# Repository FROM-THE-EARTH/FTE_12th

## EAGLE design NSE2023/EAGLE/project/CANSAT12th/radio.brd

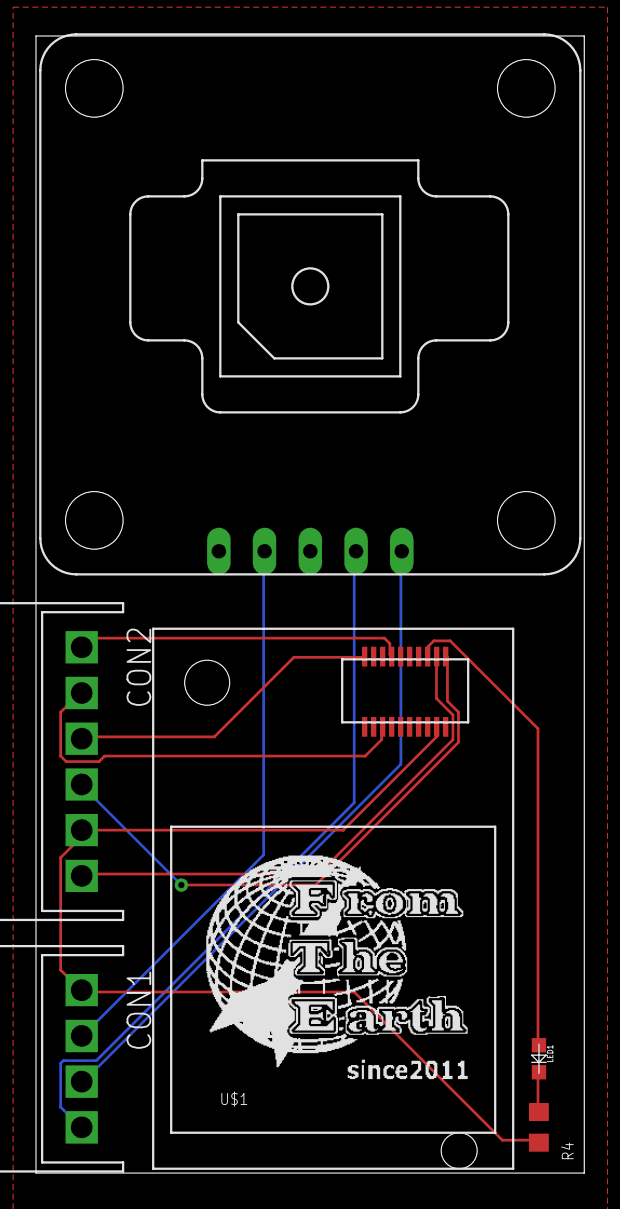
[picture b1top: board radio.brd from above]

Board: 2 copper layers, 30.5 x 63.2 mm, 7 parts (0 on the bottom side), 11 nets.

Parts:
CON1: 4PIN_SIDE
CON2: 6PIN_SIDE
IM: IM920C
LED1: OSXX1608C1A
R4: 100; R0603
U$1: LOGO
U$3: AE-GYSFDMAXB

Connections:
+3V3: CON2.P$6, IM.$P17
+5V: CON1.P$2, U$3.P4
GND: CON1.P$1, CON2.P$5, IM.$P18, R4.1
GPSRX: CON1.P$3, U$3.P2
GPSTX: CON1.P$4, U$3.P1
IM_BUSY: CON2.P$3, IM.$P1
IM_RESET: CON2.P$4, IM.$P19
IM_RX: CON2.P$2, IM.$P6
IM_TX: CON2.P$1, IM.$P7
LED: IM.$P15, LED1.AN
unnamed: LED1.CT, R4.2

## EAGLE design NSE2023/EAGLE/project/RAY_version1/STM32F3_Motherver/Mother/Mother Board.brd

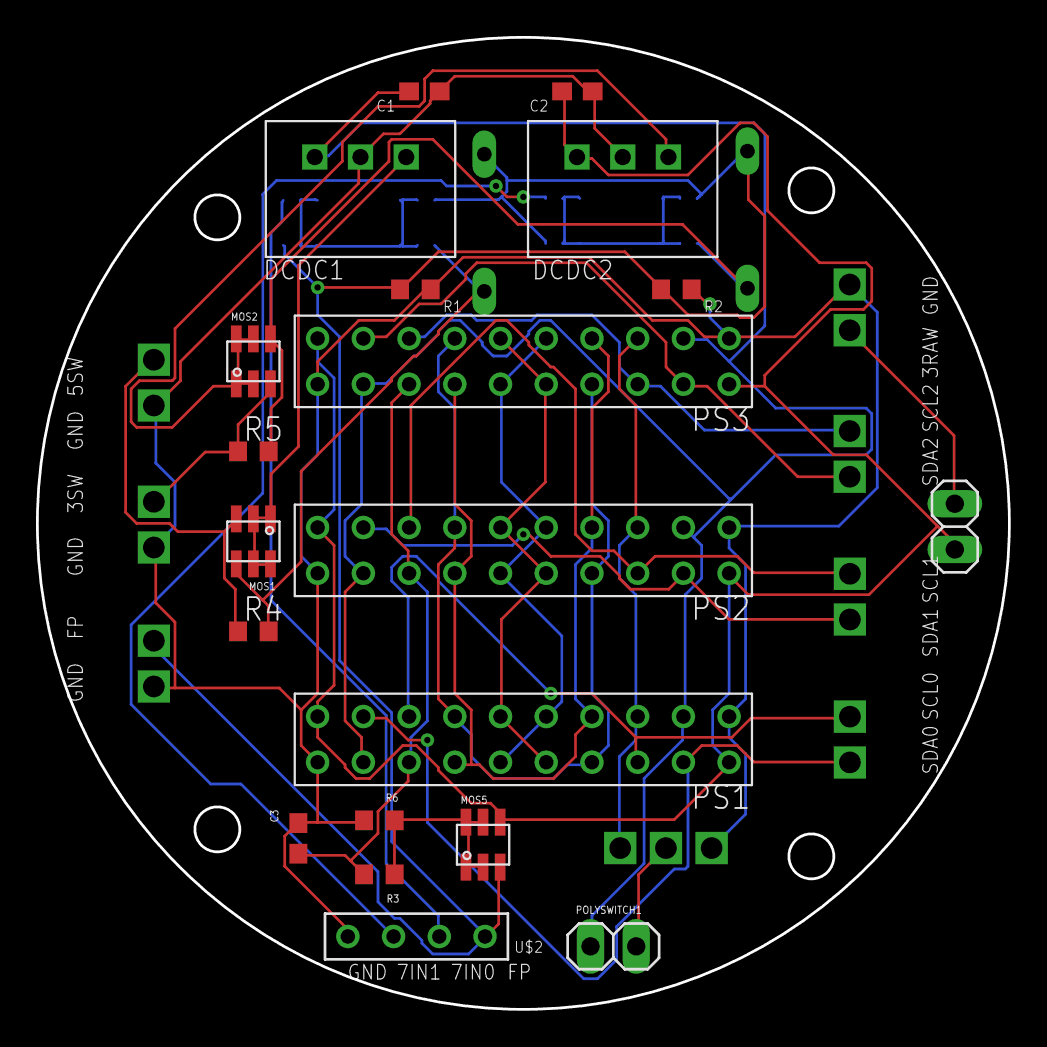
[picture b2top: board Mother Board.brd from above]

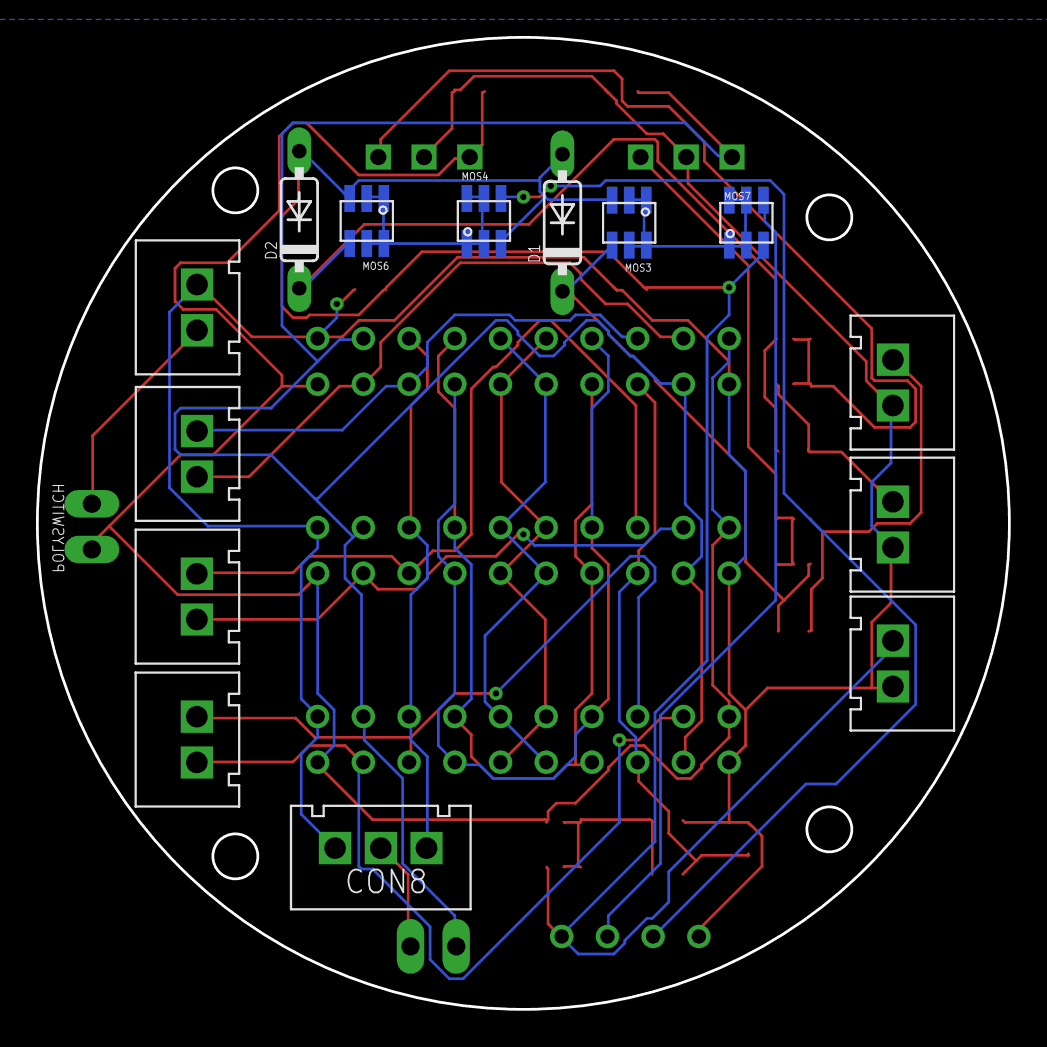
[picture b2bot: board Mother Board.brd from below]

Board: 2 copper layers, 54.0 x 54.0 mm, 34 parts (14 on the bottom side), 29 nets.

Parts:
C1, C2: 3.3uF; C0603
C3: 10uF; C0603
CON1, CON2, CON3, CON4, CON5, CON6, CON7: 2PIN
CON8: 3PIN
D1, D2: 1N4148DO35-7; DO35-7
DCDC1: 5V1A_M78AR05-1
DCDC2: 3.3V1A_M78AR033-1
MOS1, MOS2, MOS3, MOS4, MOS5, MOS6, MOS7: SSM6J808R
POLYSWITCH, POLYSWITCH1: 1X02
PS1, PS2, PS3: 2X10
R1, R2, R3: 1k; R0603
R4, R5: 100k; R0603
R6: 10k; R0603
U$2: 1X4

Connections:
3.3VSW: CON7.P$2, MOS2.3, R5.1
3.3_RAW: CON4.P$2, POLYSWITCH.2
5VSW: CON6.P$2, MOS1.3, R4.1
5V_RAW: CON8.P$2, POLYSWITCH1.2
7.4_0ENT: MOS7.4, U$2.P$2
7.4_1ENT: MOS4.4, U$2.P$3
+3V3: C2.1, DCDC2.VOUT, MOS5.4, POLYSWITCH.1, PS1.P$2, PS1.P$19, PS2.P$2, PS2.P$19, PS3.P$2, PS3.P$19
+5V: C1.1, DCDC1.VOUT, POLYSWITCH1.1, PS1.P$3, PS1.P$18, PS2.P$3, PS2.P$18, PS3.P$3, PS3.P$18
+5V1: DCDC1.VIN, MOS1.1, MOS1.2, MOS1.5, MOS1.6
BIT1: PS1.P$9, PS1.P$12, PS2.P$9, PS2.P$12, PS3.P$9, PS3.P$12
BIT2: PS1.P$7, PS1.P$14, PS2.P$7, PS2.P$14, PS3.P$7, PS3.P$14
FP: CON5.P$2, D1.A, D2.A, MOS3.3, MOS4.3, MOS5.3, MOS6.3, MOS7.3, R1.2, R2.2, U$2.P$1
FP_CHECKER: C3.1, PS1.P$5, PS2.P$5, PS3.P$5, R3.2
GND: C1.2, C2.2, C3.2, CON4.P$1, CON5.P$1, CON6.P$1, CON7.P$1, CON8.P$1, DCDC1.GND, DCDC2.GND, PS1.P$1, PS1.P$20, PS2.P$1, PS2.P$20, PS3.P$1, PS3.P$20, R1.1, R2.1, R6.1, U$2.P$4
LOGRX: PS1.P$8, PS1.P$13, PS2.P$8, PS2.P$13, PS3.P$8, PS3.P$13
LOGTX: PS1.P$10, PS1.P$11, PS2.P$10, PS2.P$11, PS3.P$10, PS3.P$11
unnamed: D2.C, MOS2.4, MOS6.4, R5.2
unnamed: MOS4.1, MOS4.2, MOS4.5, MOS4.6, MOS6.1, MOS6.2, MOS6.5, MOS6.6
unnamed: DCDC2.VIN, MOS2.1, MOS2.2, MOS2.5, MOS2.6
unnamed: D1.C, MOS1.4, MOS3.4, R4.2
unnamed: MOS3.1, MOS3.2, MOS3.5, MOS3.6, MOS7.1, MOS7.2, MOS7.5, MOS7.6
unnamed: MOS5.1, MOS5.2, MOS5.5, MOS5.6, R3.1, R6.2
PWM: CON8.P$3, PS1.P$16, PS2.P$16, PS3.P$16
SCL0: CON1.P$1, PS1.P$6, PS1.P$15
SCL1: CON2.P$1, PS2.P$6, PS2.P$15
SCL2: CON3.P$1, PS3.P$6, PS3.P$15
SDA0: CON1.P$2, PS1.P$4, PS1.P$17
SDA1: CON2.P$2, PS2.P$4, PS2.P$17
SDA2: CON3.P$2, PS3.P$4, PS3.P$17

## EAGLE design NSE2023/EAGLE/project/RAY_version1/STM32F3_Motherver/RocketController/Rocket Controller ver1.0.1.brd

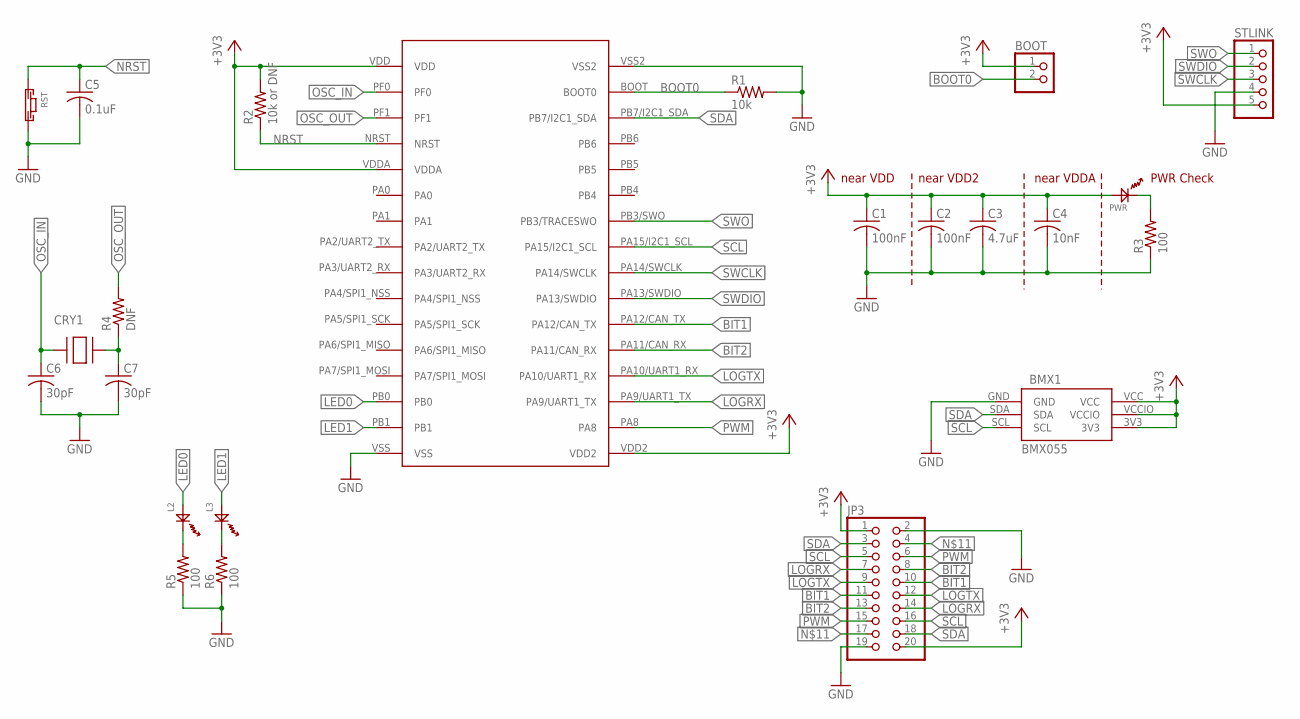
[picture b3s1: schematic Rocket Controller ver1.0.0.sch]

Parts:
BMX1: BMX055
BOOT: PINHD-1X2; 1X02
C1, C2: 100nF; C1608
C3: 4.7uF; C1608
C4: 10nF; C1608
C5: 0.1uF; C1608
C6, C7: 30pF; C1608
CRY1: 8MHZ; CRYSTAL
JP3: PINHD-2X10/90; 2X10/90
L2, L3: OSXX1608C1A
PWR: OSXX1608C1A
R1: 10k; R0603
R2: 10k or DNF; R0603
R3, R5, R6: 100; R0603
R4: DNF; R0603
RST: TVAF06-A020B-R
STLINK: PINHD-1X5; 1X05
U$1: STM32F303K8

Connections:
+3V3: BMX1.3V3, BMX1.VCC, BMX1.VCCIO, BOOT.1, C1.1, C2.1, C3.1, C4.1, JP3.1, JP3.20, PWR.AN, R2.2, STLINK.5, U$1.VDD, U$1.VDD2, U$1.VDDA
BIT1: JP3.10, JP3.11, U$1.PA12/CAN_TX
BIT2: JP3.8, JP3.13, U$1.PA11/CAN_RX
BOOT0: BOOT.2, R1.1, U$1.BOOT (BOOT0)
GND: BMX1.GND, C1.2, C2.2, C3.2, C4.2, C5.2, C6.2, C7.2, JP3.2, JP3.19, R1.2, R3.1, R5.1, R6.1, RST.P$2, STLINK.4, U$1.VSS, U$1.VSS2
LED0: L2.AN, U$1.PB0; also elsewhere on the board
LED1: L3.AN, U$1.PB1; also elsewhere on the board
LOGRX: JP3.7, JP3.14, U$1.PA9/UART1_TX
LOGTX: JP3.9, JP3.12, U$1.PA10/UART1_RX
unnamed: PWR.CT, R3.2
unnamed 10: L2.CT, R5.2; also elsewhere on the board
unnamed: C7.1, CRY1.P$2, R4.1
unnamed 12: L3.CT, R6.2; also elsewhere on the board
unnamed: JP3.4, JP3.17
NRST: C5.1, R2.1, RST.P$1, U$1.NRST
OSC_IN: C6.1, CRY1.P$1, U$1.PF0
OSC_OUT: R4.2, U$1.PF1
SCL: BMX1.SCL, JP3.5, JP3.16, U$1.PA15/I2C1_SCL
SDA: BMX1.SDA, JP3.3, JP3.18, U$1.PB7/I2C1_SDA
SWCLK: STLINK.3, U$1.PA14/SWCLK
SWDIO: STLINK.2, U$1.PA13/SWDIO
SWO: STLINK.1, U$1.PB3/SWO (PB3/TRACESWO)

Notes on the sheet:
near VDD
near VDD2
near VDDA
PWR Check

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
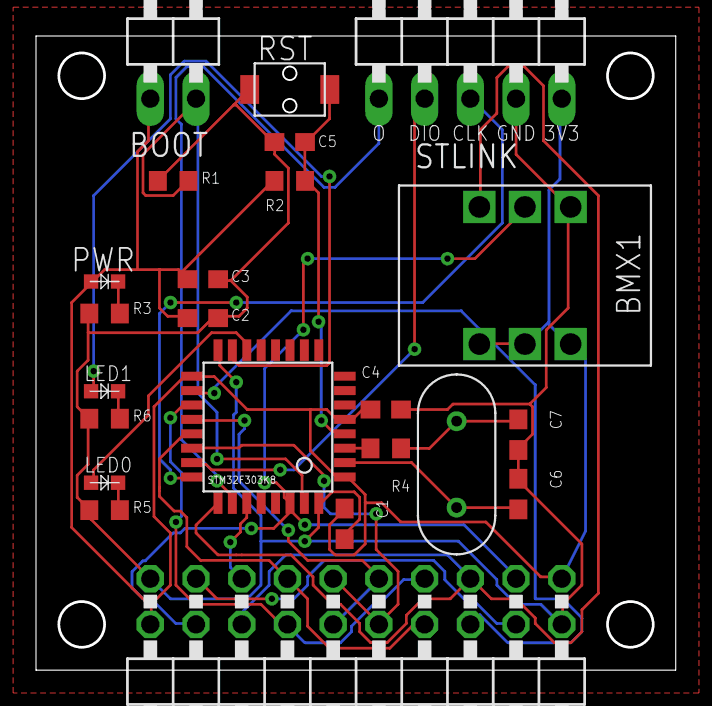
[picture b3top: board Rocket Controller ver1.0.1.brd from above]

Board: 2 copper layers, 35.5 x 35.2 mm, 23 parts (0 on the bottom side), 24 nets.

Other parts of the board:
LED0, LED1: OSXX1608C1A

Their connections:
LED0: LED0.AN; also elsewhere on the board
LED1: LED1.AN; also elsewhere on the board
unnamed 10: LED0.CT; also elsewhere on the board
unnamed 12: LED1.CT; also elsewhere on the board

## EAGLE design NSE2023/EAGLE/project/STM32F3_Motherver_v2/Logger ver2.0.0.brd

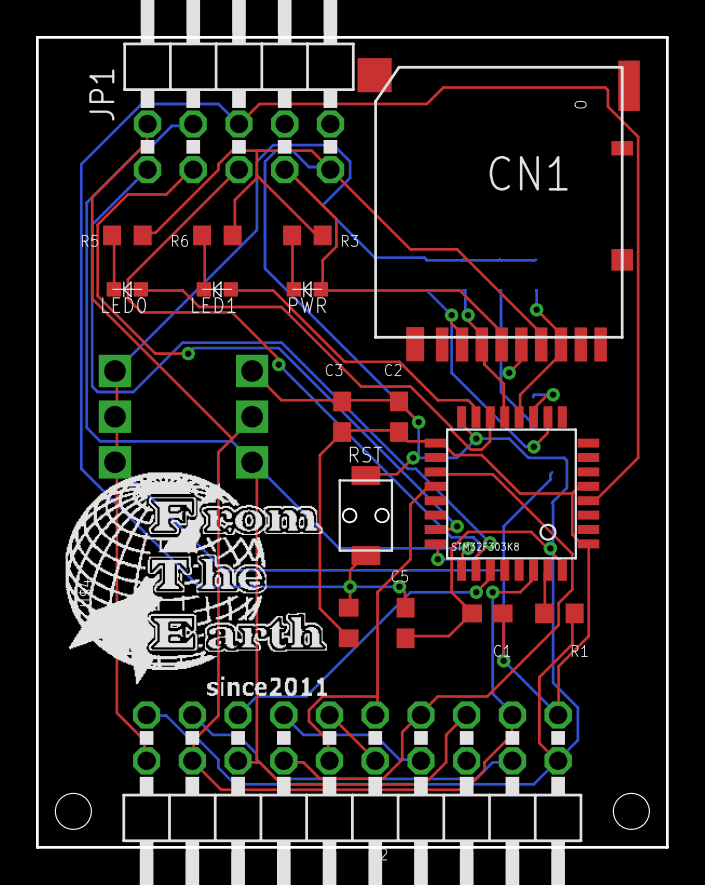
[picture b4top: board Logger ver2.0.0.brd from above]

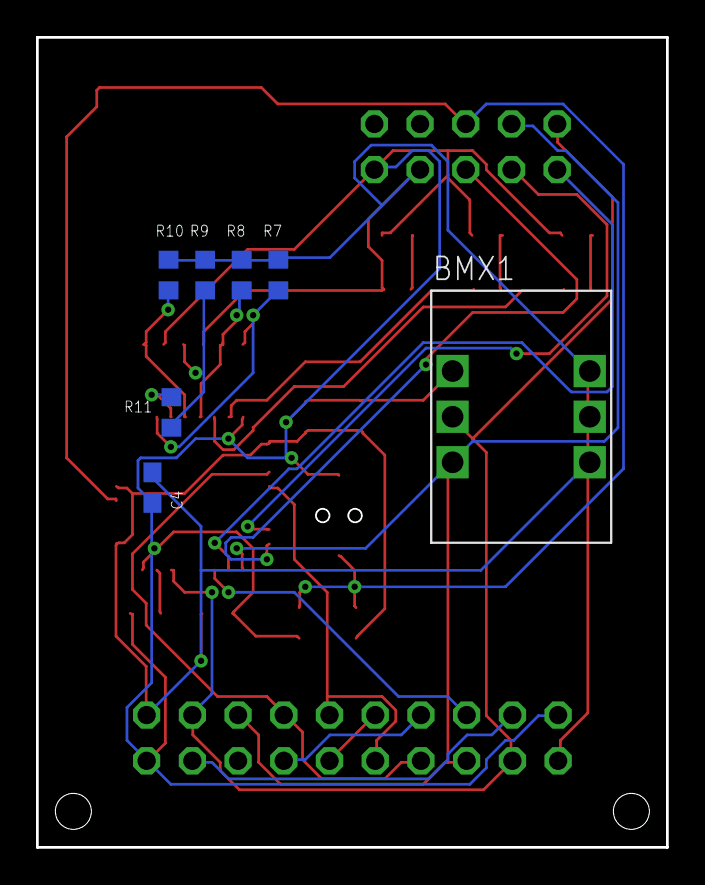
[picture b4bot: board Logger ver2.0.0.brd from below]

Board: 2 copper layers, 35.0 x 45.0 mm, 25 parts (7 on the bottom side), 25 nets.

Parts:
BMX1: BMX055
C1, C2: 100nF; C1608
C3: 4.7uF; C1608
C4: 10nF; C1608
C5: 0.1uF; C1608
CN1: DM3AT
JP1: 2X05/90
JP3: 2X10/90
LED0, LED1: OSXX1608C1A
PWR: OSXX1608C1A
R1, R7, R8, R9, R10: 10k; R0603
R2: 10k or DNF; R0603
R3, R5, R6, R11: 100; R0603
RST: TVAF06-A020B-R
U$1: STM32F303K8
U$4: F.T.E.LOGO; LOGO

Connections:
+3V3: BMX1.3V3, BMX1.VCC, BMX1.VCCIO, C1.1, C2.1, C3.1, C4.1, CN1.VDD, JP1.7, JP3.1, JP3.20, PWR.AN, R2.2, R7.2, R8.2, R9.2, R10.2, U$1.VDD, U$1.VDD2, U$1.VDDA
BIT1: JP3.10, JP3.11
BIT2: JP3.8, JP3.13
BOOT0: R1.1, U$1.BOOT
FP_CHECKER: JP3.15, U$1.PB4
GND: BMX1.GND, C1.2, C2.2, C3.2, C4.2, C5.2, CN1.VSS, JP1.9, JP3.2, JP3.19, R1.2, R3.1, R5.1, R6.1, RST.P$2, U$1.VSS, U$1.VSS2
LED0: LED0.AN, U$1.PB0
LED1: LED1.AN, U$1.PB1
LOGRX: JP3.7, JP3.14, U$1.PA9/UART1_TX
LOGTX: JP3.9, JP3.12, U$1.PA10/UART1_RX
MISO: CN1.DAT0, R10.1, U$1.PA6/SPI1_MISO
MOSI: CN1.CMD, R8.1, U$1.PA7/SPI1_MOSI
unnamed: PWR.CT, R3.2
unnamed: LED0.CT, R5.2
unnamed: LED1.CT, R6.2
unnamed: CN1.CLK, R9.1, R11.2
unnamed: JP3.4, JP3.17
NRST: C5.1, JP1.6, R2.1, RST.P$1, U$1.NRST
NSS: CN1.CD/DAT3, R7.1, U$1.PA4/SPI1_NSS
SCK: R11.1, U$1.PA5/SPI1_SCK
SCL: BMX1.SCL, JP1.4, JP3.5, JP3.16, U$1.PA15/I2C1_SCL
SDA: BMX1.SDA, JP1.2, JP3.3, JP3.18, U$1.PB7/I2C1_SDA
SWCLK: JP1.5, U$1.PA14/SWCLK
SWDIO: JP1.3, U$1.PA13/SWDIO
SWO: JP1.1, U$1.PB3/SWO

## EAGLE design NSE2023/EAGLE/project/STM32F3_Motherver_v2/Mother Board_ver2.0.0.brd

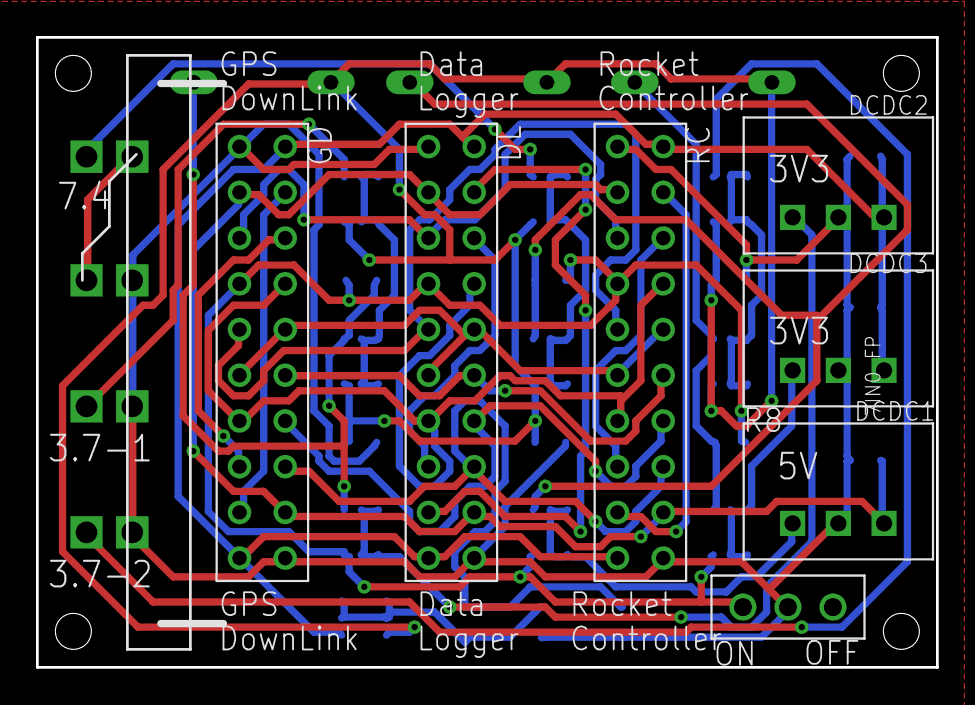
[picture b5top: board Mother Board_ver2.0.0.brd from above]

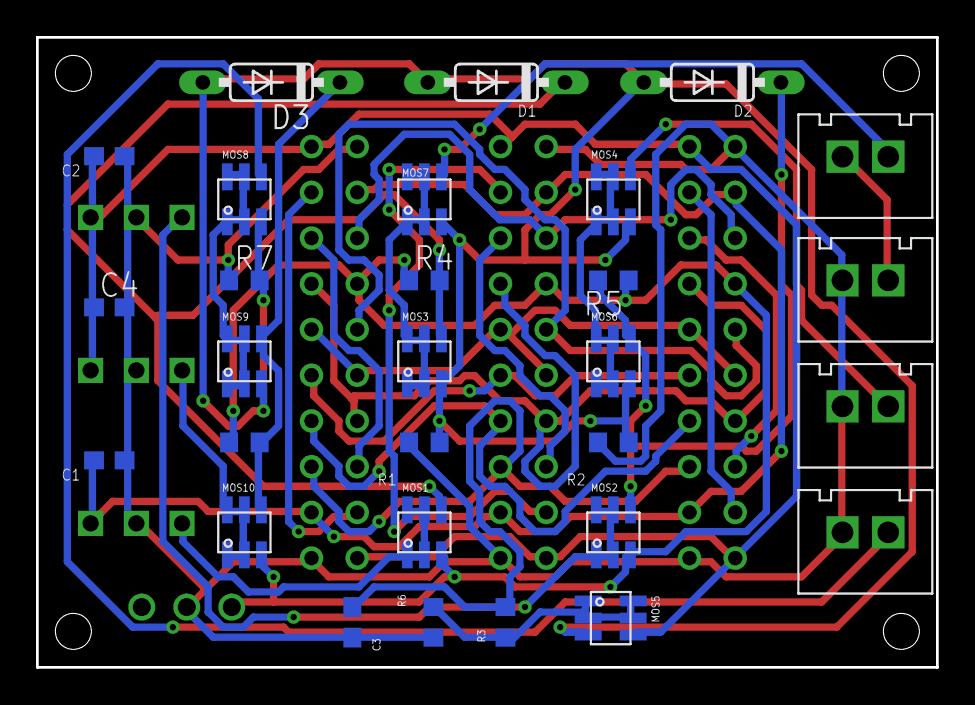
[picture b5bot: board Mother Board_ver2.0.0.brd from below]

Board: 2 copper layers, 50.0 x 35.0 mm, 36 parts (29 on the bottom side), 32 nets.

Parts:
C1, C2, C4: 3.3uF; C0603
C3: 10uF; C0603
CON1, CON2, CON3, CON4: 2PIN
D1, D2, D3: 1N4148DO35-7; DO35-7
DCDC1: 5V1A_M78AR05-1
DCDC2, DCDC3: 3.3V1A_M78AR033-1
DL: 2X10
GD: 2X10
MOS1, MOS2, MOS3, MOS4, MOS5, MOS6, MOS7, MOS8, MOS9, MOS10: SSM6J808R
R1, R2, R3, R7: 1k; R0603
R4, R5, R8: 100k; R0603
R6: 10k; R0603
RC: 2X10
SW1: SRIDE_SWITCH

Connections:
3.3_RAW1: CON4.P$2, MOS7.4
3.3_RAW2: CON1.P$2, CON4.P$1
3.3_RAW3: CON2.P$2, MOS4.4
3.3_RAW4: CON3.P$2, MOS8.4
+3V3: C2.1, C4.1, DCDC2.VOUT, DCDC3.VOUT, DL.P$2, DL.P$19, GD.P$2, GD.P$19, MOS5.4, RC.P$2, RC.P$19
+5V: C1.1, DCDC1.VOUT, DL.P$3, DL.P$18, GD.P$3, GD.P$18, RC.P$3, RC.P$18
+5V1: DCDC1.VIN, MOS1.1, MOS1.2, MOS1.5, MOS1.6
BIT1: DL.P$9, GD.P$9, RC.P$9
BIT2: DL.P$7, GD.P$7, RC.P$7
FP: D1.A, D2.A, D3.A, MOS3.3, MOS4.3, MOS5.3, MOS6.3, MOS7.3, MOS8.3, MOS9.3, R1.2, R2.2, R7.2
FPRAW: DL.P$12, GD.P$12, RC.P$12
FP_CHECKER: C3.1, DL.P$5, GD.P$5, R3.2, RC.P$5
GND: C1.2, C2.2, C3.2, C4.2, CON1.P$1, CON2.P$1, CON3.P$1, DCDC1.GND, DCDC2.GND, DCDC3.GND, DL.P$1, DL.P$20, GD.P$1, GD.P$20, R1.1, R2.1, R6.1, R7.1, RC.P$1, RC.P$20, SW1.LR
LOGRX: DL.P$8, DL.P$13, GD.P$8, GD.P$13, RC.P$8, RC.P$13
LOGTX: DL.P$10, DL.P$11, GD.P$10, GD.P$11, RC.P$10, RC.P$11
unnamed: D2.C, MOS2.4, MOS6.4, R5.2
unnamed: MOS4.1, MOS4.2, MOS4.5, MOS4.6, MOS6.1, MOS6.2, MOS6.5, MOS6.6
unnamed: D3.C, MOS9.4, MOS10.4, R8.2
unnamed: MOS8.1, MOS8.2, MOS8.5, MOS8.6, MOS9.1, MOS9.2, MOS9.5, MOS9.6
unnamed: DCDC2.VIN, MOS2.1, MOS2.2, MOS2.5, MOS2.6
unnamed: DCDC3.VIN, MOS10.1, MOS10.2, MOS10.5, MOS10.6
unnamed: D1.C, MOS1.4, MOS3.4, R4.2
unnamed: MOS3.1, MOS3.2, MOS3.5, MOS3.6, MOS7.1, MOS7.2, MOS7.5, MOS7.6
unnamed: MOS5.1, MOS5.2, MOS5.5, MOS5.6, R3.1, R6.2
PWM: DL.P$16, GD.P$16, RC.P$16
SCL0: RC.P$6, RC.P$15
SCL1: DL.P$6, DL.P$15
SCL2: GD.P$6, GD.P$15
SDA0: RC.P$4, RC.P$17
SDA1: DL.P$4, DL.P$17
SDA2: GD.P$4, GD.P$17
SW: DL.P$14, GD.P$14, MOS1.3, MOS2.3, MOS10.3, R4.1, R5.1, R8.1, RC.P$14, SW1.L

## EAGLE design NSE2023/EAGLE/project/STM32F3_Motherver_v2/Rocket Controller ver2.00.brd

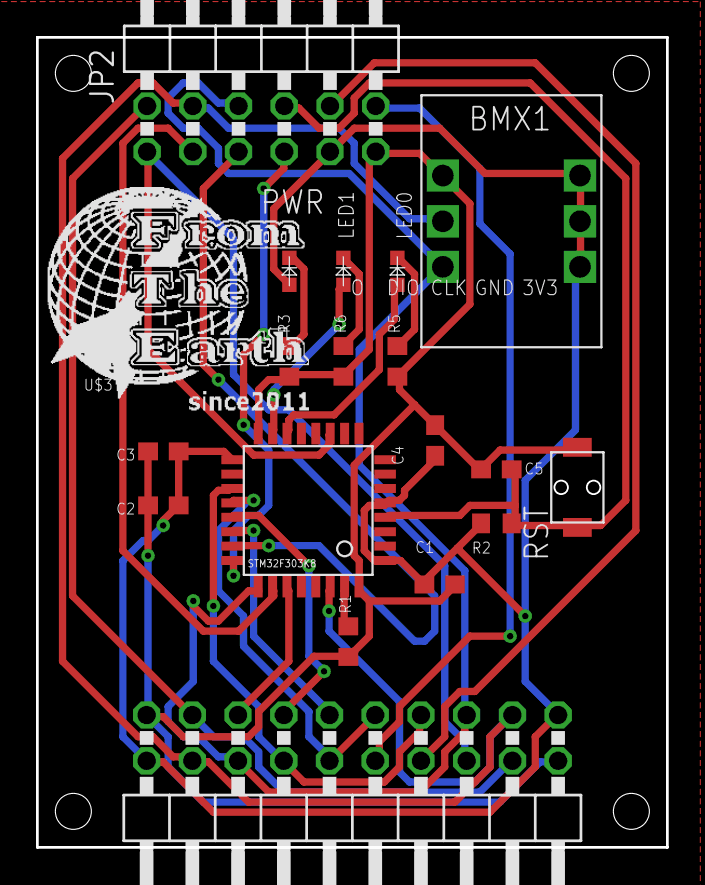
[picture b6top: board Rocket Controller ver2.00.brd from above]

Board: 2 copper layers, 35.0 x 45.0 mm, 19 parts (0 on the bottom side), 23 nets.

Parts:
BMX1: BMX055
C1, C2: 100nF; C1608
C3: 4.7uF; C1608
C4: 10nF; C1608
C5: 0.1uF; C1608
JP2: 2X06/90
JP3: 2X10/90
LED0, LED1: OSXX1608C1A
PWR: OSXX1608C1A
R1: 10k; R0603
R2: 10k or DNF; R0603
R3, R5, R6: 100; R0603
RST: TVAF06-A020B-R
U$1: STM32F303K8
U$3: F.T.E.LOGO; LOGO

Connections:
+3V3: BMX1.3V3, BMX1.VCC, BMX1.VCCIO, C1.1, C2.1, C3.1, C4.1, JP2.9, JP3.1, JP3.20, PWR.AN, R2.2, U$1.VDD, U$1.VDD2, U$1.VDDA
+5V: JP2.2, JP3.4, JP3.17
BIT1: JP3.11, U$1.PA12/CAN_TX
BIT2: JP3.13, U$1.PA11/CAN_RX
BOOT0: R1.1, U$1.BOOT
FPRAW: JP2.12, JP3.10
FP_CHECKER: JP3.15, U$1.PB4
GND: BMX1.GND, C1.2, C2.2, C3.2, C4.2, C5.2, JP2.11, JP3.2, JP3.19, R1.2, R3.1, R5.1, R6.1, RST.P$2, U$1.VSS, U$1.VSS2
LED0: LED0.AN, U$1.PB0
LED1: LED1.AN, U$1.PB1
LOGRX: JP3.7, JP3.14, U$1.PA9/UART1_TX
LOGTX: JP3.9, JP3.12, U$1.PA10/UART1_RX
unnamed: PWR.CT, R3.2
unnamed: LED0.CT, R5.2
unnamed: LED1.CT, R6.2
NRST: C5.1, JP2.8, R2.1, RST.P$1, U$1.NRST
PWM: JP2.1, JP3.6, U$1.PA5/SPI1_SCK
SCL: BMX1.SCL, JP2.6, JP3.5, JP3.16, U$1.PA15/I2C1_SCL
SDA: BMX1.SDA, JP2.4, JP3.3, JP3.18, U$1.PB7/I2C1_SDA
SW: JP2.10, JP3.8
SWCLK: JP2.7, U$1.PA14/SWCLK
SWDIO: JP2.5, U$1.PA13/SWDIO
SWO: JP2.3, U$1.PB3/SWO
